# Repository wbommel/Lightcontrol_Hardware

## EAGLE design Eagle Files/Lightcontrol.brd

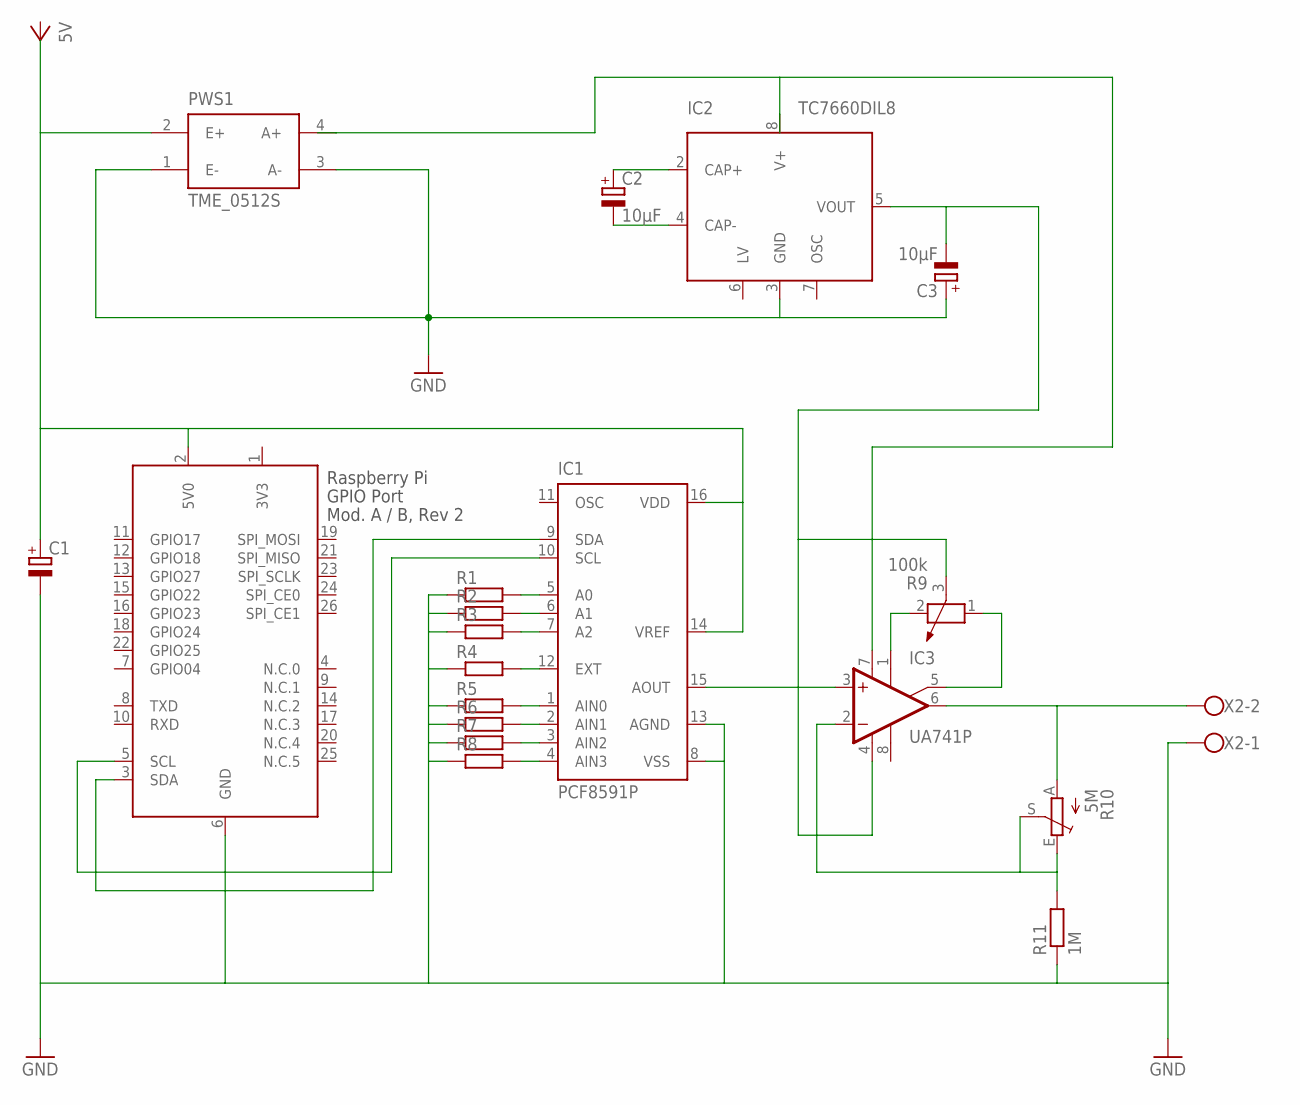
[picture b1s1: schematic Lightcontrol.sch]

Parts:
C1: CPOL-EUE1.8-4; E1,8-4
C2, C3: 10µF; E1,8-4
IC1: PCF8591P; DIL16
IC2: TC7660DIL8; DIL8
IC3: UA741P; DIL08
PWS1: TME_0512S; TMEXXXXS
R1, R2, R3, R4, R5, R6, R7, R8: R-EU_0204/5; 0204/5
R9: 100k; PT-10S
R10: 5M; ST15
R11: 1M; 0204/5
X1: RASPI_GPIO_AB_PIN
X2: W237-102

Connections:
3V3: X1.1 (3V3)
GND: C1.-, C3.+, IC1.8 (VSS), IC1.13 (AGND), IC2.3 (GND), PWS1.1 (E-), PWS1.3 (A-), R1.1, R2.1, R3.1, R4.1, R5.1, R6.1, R7.1, R8.1, R11.1, X1.6 (GND), X2.1
unnamed: IC1.15 (AOUT), IC3.3 (+IN)
unnamed: IC3.1 (ON1), R9.2
unnamed: C3.-, IC2.5 (VOUT), IC3.4 (V-), R9.3
unnamed: IC1.9 (SDA), X1.3 (SDA)
unnamed: IC1.10 (SCL), X1.5 (SCL)
unnamed: IC1.5 (A0), R1.2
unnamed: IC1.6 (A1), R2.2
unnamed: IC1.7 (A2), R3.2
unnamed: IC1.12 (EXT), R4.2
unnamed: IC1.1 (AIN0), R5.2
unnamed: IC1.2 (AIN1), R6.2
unnamed: IC1.3 (AIN2), R7.2
unnamed: IC1.4 (AIN3), R8.2
unnamed: IC3.5 (ON2), R9.1
unnamed: C1.+, IC1.14 (VREF), IC1.16 (VDD), PWS1.2 (E+), X1.2 (5V0)
unnamed: IC3.6 (OUT), R10.A, X2.2
unnamed: IC3.2 (-IN), R10.E, R10.S, R11.2
unnamed: IC2.8 (V+), IC3.7 (V+), PWS1.4 (A+)
unnamed: C2.+, IC2.2 (CAP+)
unnamed: C2.-, IC2.4 (CAP-)

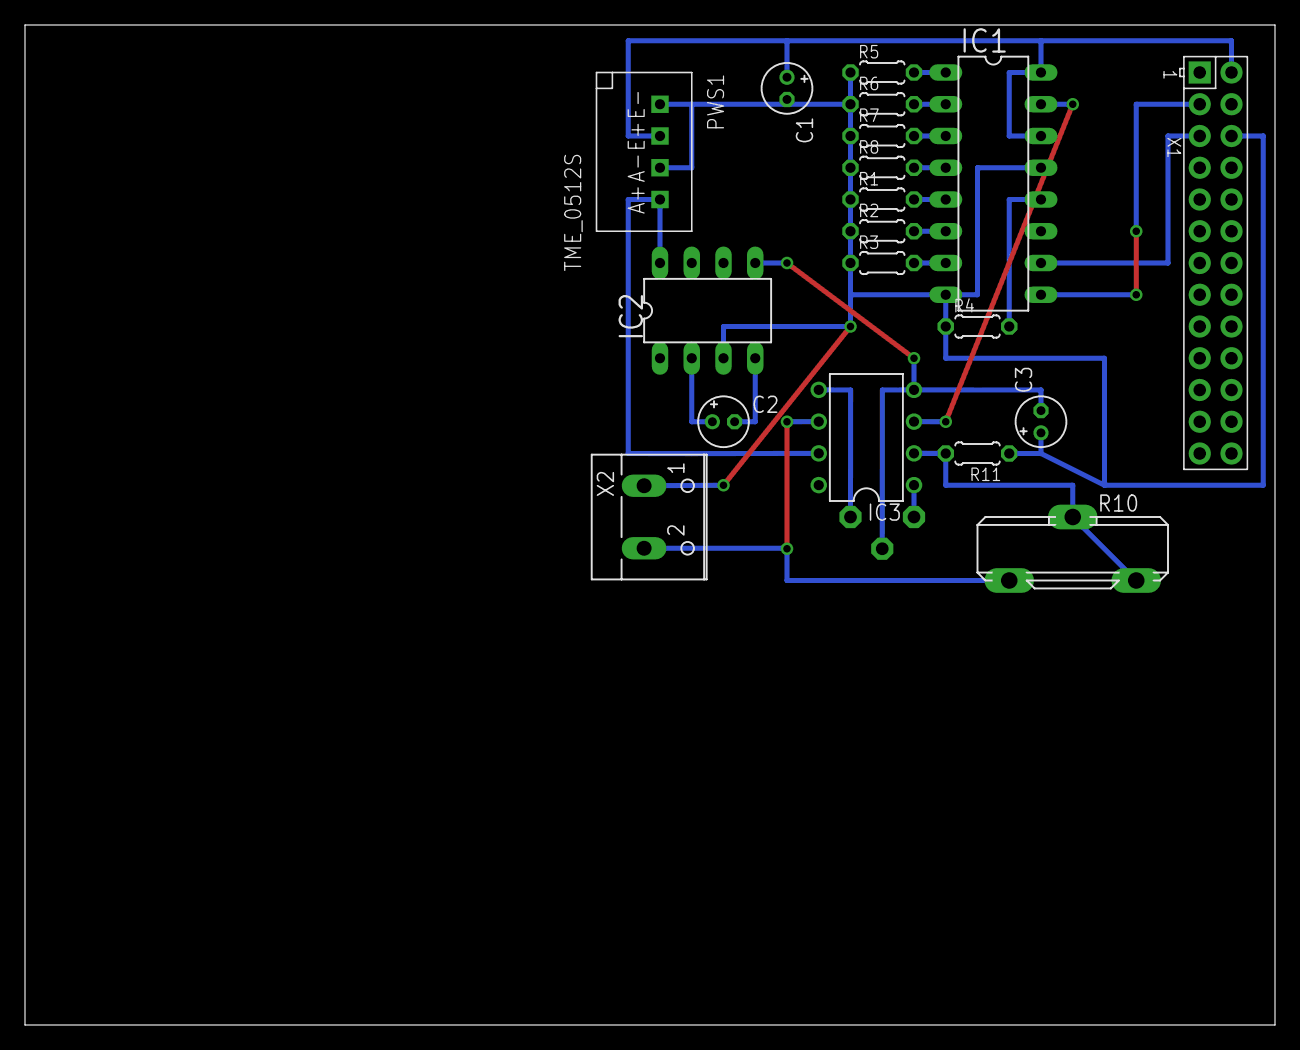
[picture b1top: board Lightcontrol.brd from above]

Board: 2 copper layers, 100.0 x 80.0 mm, 20 parts (1 on the bottom side), 21 nets.

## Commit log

2019-02-17 Added stuff
